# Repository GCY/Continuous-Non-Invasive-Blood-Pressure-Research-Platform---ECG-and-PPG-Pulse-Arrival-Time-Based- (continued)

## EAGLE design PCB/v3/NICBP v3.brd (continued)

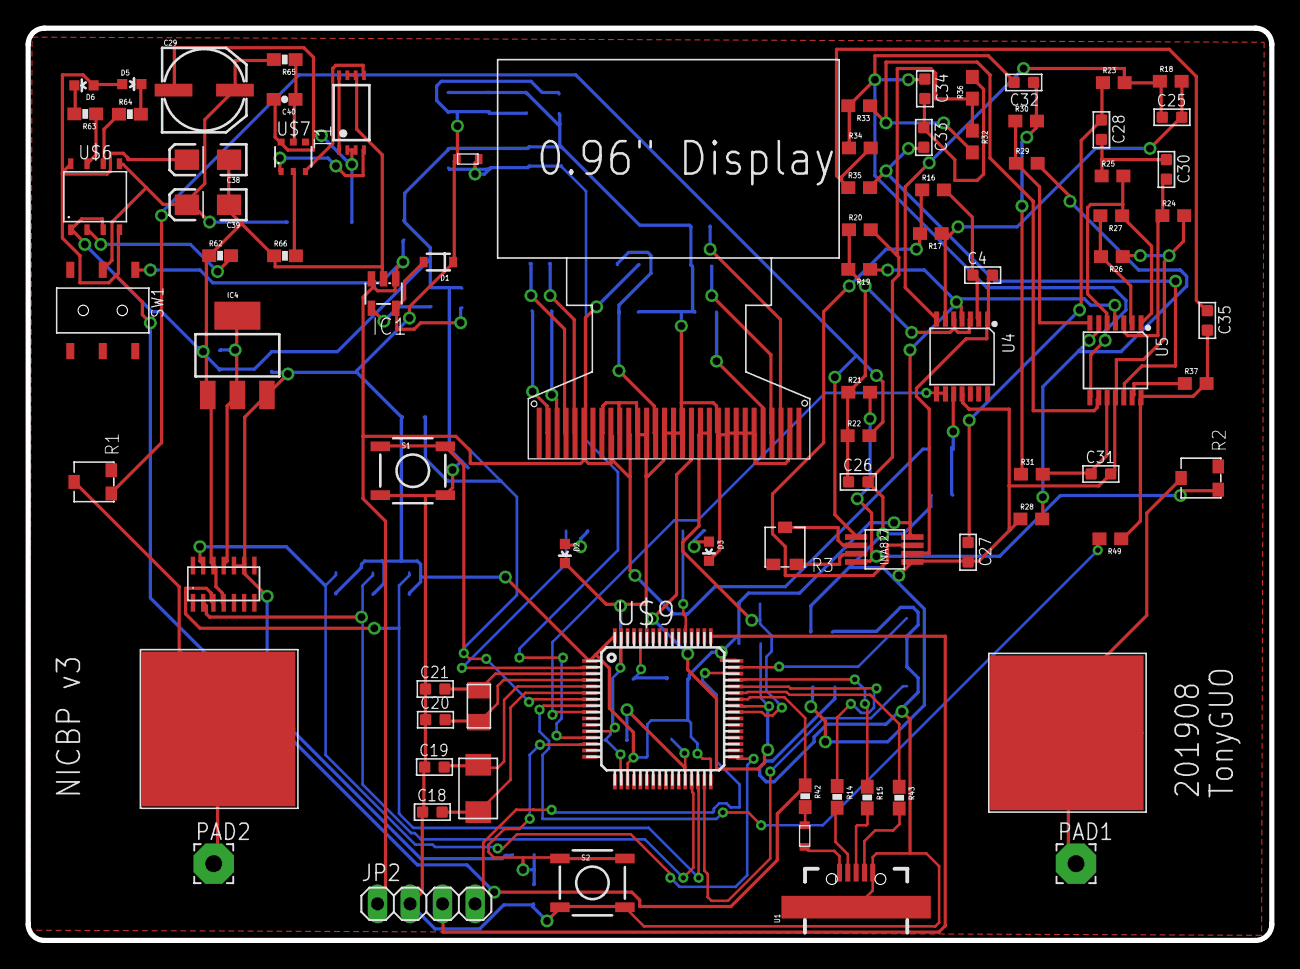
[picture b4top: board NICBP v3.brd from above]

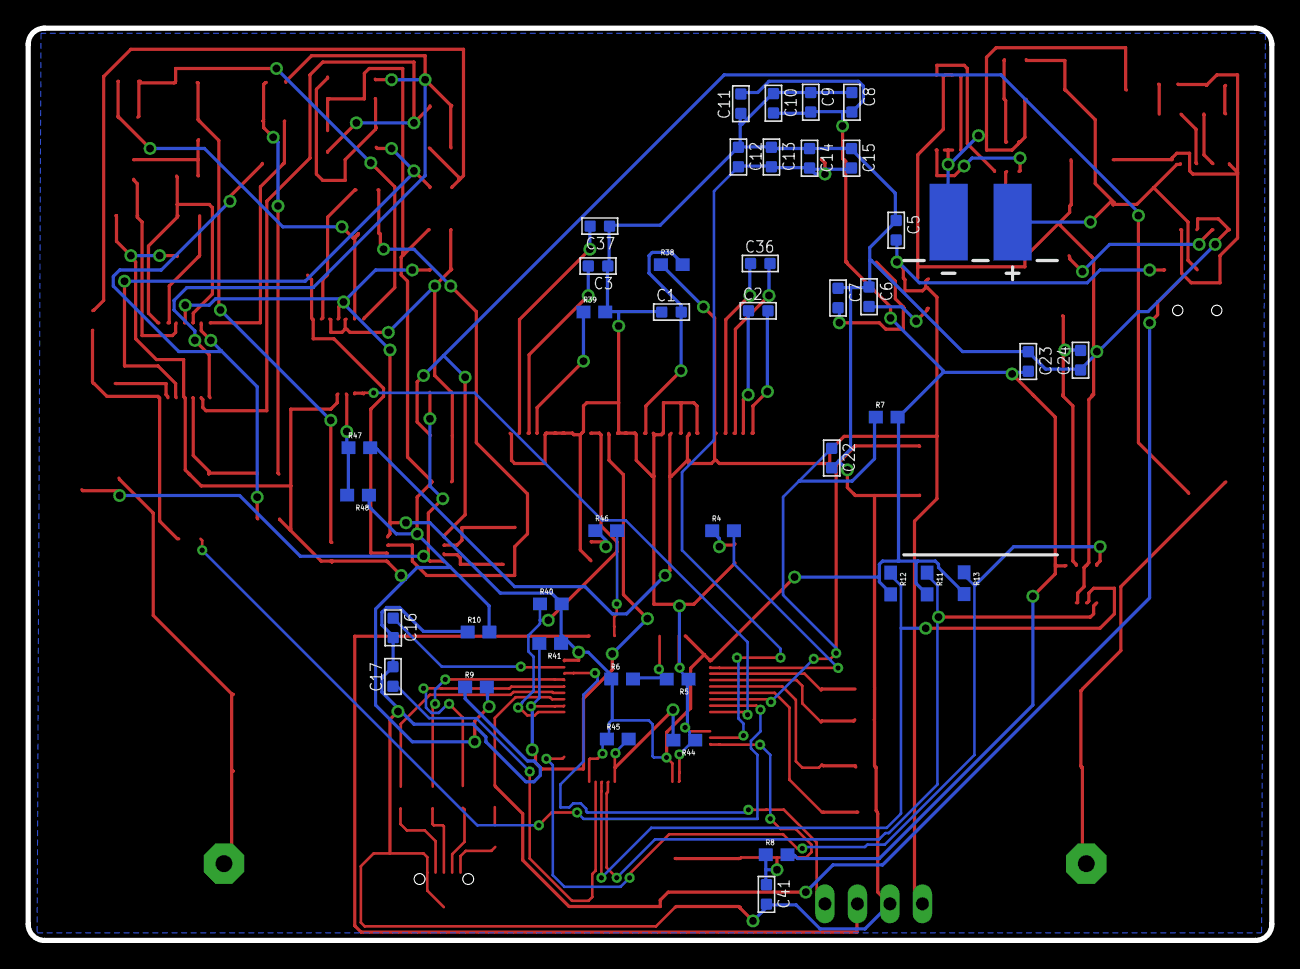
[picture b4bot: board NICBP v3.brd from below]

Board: 2 copper layers, 97.2 x 71.3 mm, 125 parts (42 on the bottom side), 89 nets.

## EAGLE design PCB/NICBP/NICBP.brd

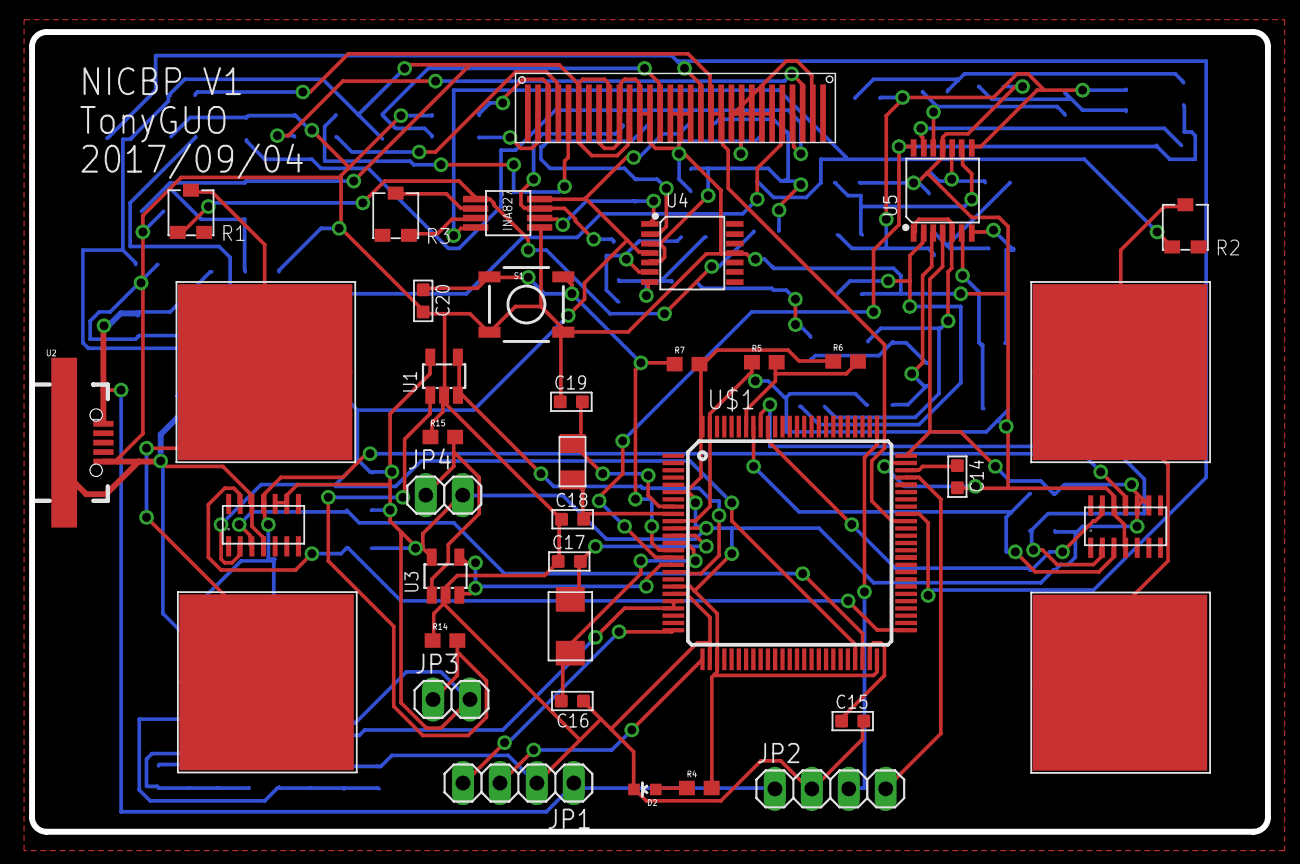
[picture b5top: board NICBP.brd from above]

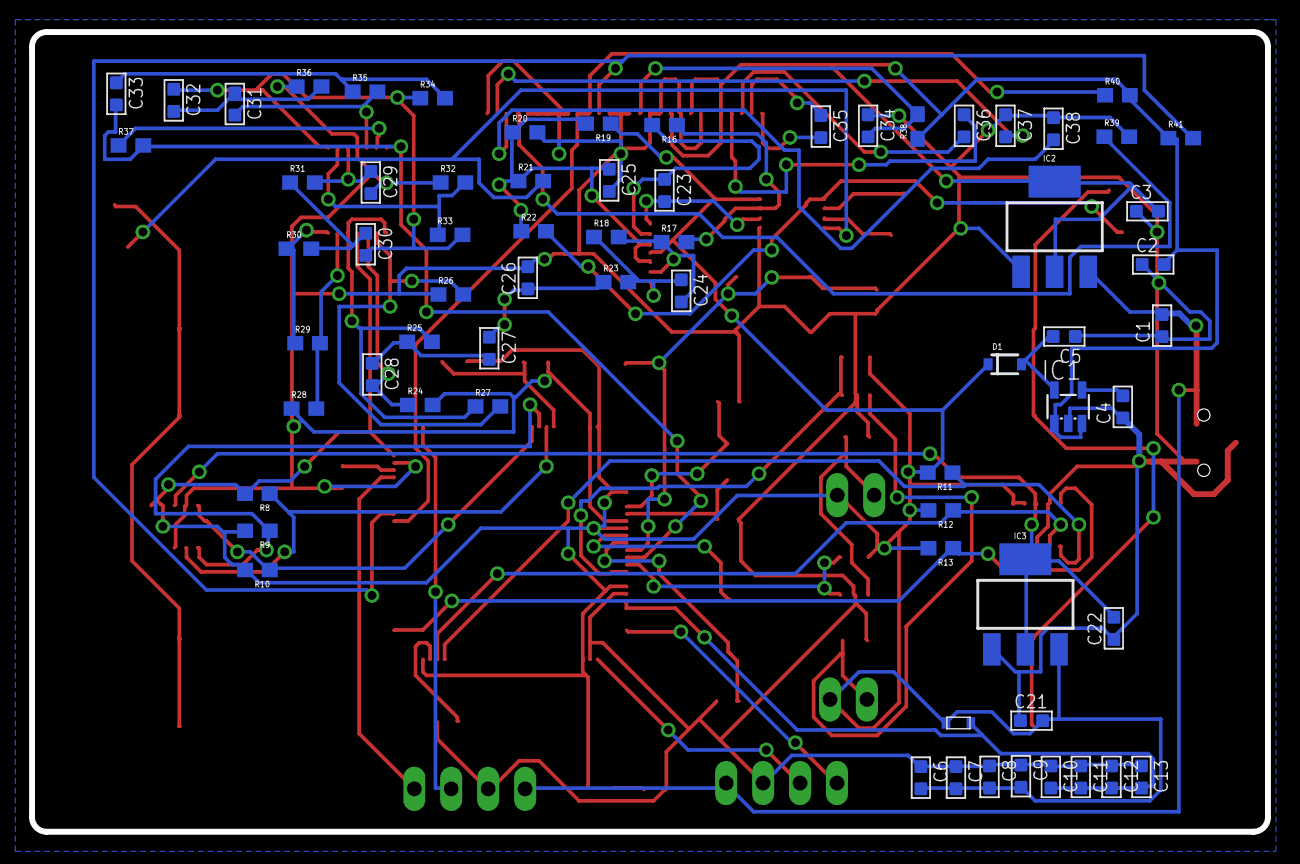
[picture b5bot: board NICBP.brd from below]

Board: 2 copper layers, 85.0 x 55.0 mm, 106 parts (68 on the bottom side), 69 nets.

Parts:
C1, C2, C3, C4, C5, C6, C7, C10, C11, C12, C13, C20, C21, C22, C23, C24, C25, C26, C27, C28, C29, C30, C31, C32, C34: 0.1uf; C0603
C8, C9, C35, C36, C37: 1uf; C0603
C14, C15: 2.2uf; C0603
C16, C17: 22pF; C0603
C18, C19: 12.5pF; C0603
C33: 0.22uf; C0603
C38: 4.7uf; C0603
D1: BAT20JFILM; SOD-323
D2: BLUE; LED-0603
IC1: LD398530RM; SOT23-5L
IC2: LDO_5V; SOT223
IC3: LDO_1V8; SOT223
JP1, JP2: 1X04
JP3, JP4: 1X02
R1, R2: 1M; TRIMPOT_TC33
R3: 100k; TRIMPOT_TC33
R4: 1k; 0603
R5, R6, R7, R19, R20, R38: 10k; 0603
R8, R9, R10, R11, R12, R13, R40, R41: 4.7k; 0603
R14, R15: 3k; 0603
R16: 1M; 0603
R17, R18, R27: 5.1k; 0603
R21, R22: 2M; 0603
R23: 100; 0603
R24, R25: 1.8M; 0603
R26, R28, R32, R37: 12k; 0603
R29: 100k; 0603
R30, R31: 7.5k; 0603
R33: 5.6k; 0603
R34, R35: 27k; 0603
R36: 9.1k; 0603
R39: 390k; 0603
S1: TACTILE_SWITCH_SMD
U1, U3: LM32AMF; SOT-23-5
U2: USB-MICRO-SMD
U4, U5: LM324PW-TSSOP14; TSSOP14-0.65-5X4.4MM
U$1: STM32F407V; TQFP100
U$2: NX5032CA-8MHZ
U$3: FCM1608KF-601T03
U$4: 32.768KHZ-FC-135
U$5: INA827
U$6, U$7, U$8, U$9: CAPSENSE_PAD
U$10, U$11: MAX30100
U$12: ER-OLED0.96

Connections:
1V8: C22.2, IC3.2, IC3.4, U$10.11, U$11.11
ADC1: C33.2, R37.2, U5.14, U$1.15
ADC2: U3.3, U3.4, U$1.16
ADC3: U1.3, U1.4, U$1.17
GND: C1.1, C2.1, C3.1, C4.1, C5.1, C6.1, C7.1, C8.1, C9.1, C10.1, C11.1, C12.1, C13.1, C14.2, C15.2, C16.1, C17.1, C18.1, C19.1, C20.2, C21.1, C22.1, C25.2, C26.2, C29.2, C34.1, C37.1, C38.1, D2.C, IC1.2, IC2.1, IC3.1, JP1.2, JP2.2, R5.1, R14.1, R15.1, R20.2, R24.2, R26.1, R28.1, R32.1, R36.1, R39.2, S1.3, S1.4, U1.2, U2.GND, U2.GND1, U3.2, U4.11, U5.11, U$1.10, U$1.20, U$1.27, U$1.74, U$1.99, U$5.5, U$10.4, U$10.12, U$11.4, U$11.12, U$12.P$8, U$12.P$10, U$12.P$12, U$12.P$13, U$12.P$15, U$12.P$16, U$12.P$17, U$12.P$21, U$12.P$22, U$12.P$23, U$12.P$24, U$12.P$25, U$12.P$29
I2C1_SCL: R9.1, U$1.92, U$10.2
I2C1_SDA: R8.1, U$1.93, U$10.3
I2C2_SCL: R11.1, U$1.47, U$11.2
I2C2_SDA: R12.1, U$1.48, U$11.3
I2C3_SCL: R41.2, U$1.67, U$12.P$18
I2C3_SDA: R40.1, U$1.66, U$12.P$19, U$12.P$20
INT_EXTI5: R10.1, U$1.91, U$10.13
INT_EXTI12: R13.1, U$1.51, U$11.13
L_ARM: R1.2, U$8.P$1, U$8.P$2, U$9.P$1, U$9.P$2
MCU_3V3: C6.2, C7.2, C8.2, C9.2, C21.2, D1.1, IC3.3, JP3.2, JP4.2, R4.2, R6.1, R7.2, R8.2, R9.2, R10.2, R11.2, R12.2, R13.2, R19.1, U1.5, U3.5, U4.4, U5.4, U$1.6, U$1.11, U$1.19, U$1.28, U$1.50, U$1.75, U$1.100, U$3.1, U$5.8, U$10.9, U$10.10, U$11.9, U$11.10
unnamed: D2.A, R4.1
unnamed: C15.1, U$1.49
unnamed: C14.1, U$1.73
unnamed: R5.2, R6.2, U$1.94
unnamed: C20.1, R7.1, S1.1, S1.2, U$1.14
unnamed: C4.2, IC1.4
unnamed: C5.2, D1.2, IC1.5
unnamed: R3.3, U$5.3
unnamed: JP4.1, R15.2, U3.1
unnamed: JP3.1, R14.2, U1.1
unnamed: R3.2, U$5.2
unnamed: C23.2, U4.1, U$5.6
unnamed: R1.1, R22.2, U$5.1
unnamed: R2.1, R21.2, U$5.4
unnamed: C23.1, R16.2, U4.2
unnamed: R16.1, R17.2, U$5.7
unnamed: C24.2, R17.1, R18.2, U4.6
unnamed: C25.1, R19.2, R20.1, R21.1, R22.1, U4.3, U4.5
unnamed: C24.1, R18.1, R23.2, U4.7
unnamed: C26.1, C27.1, R23.1
unnamed: R26.2, R27.2, U5.2
unnamed: R25.2, R27.1, U5.1, U5.5
unnamed: C28.2, R24.1, U5.3
unnamed: C27.2, C28.1, R25.1
unnamed: R28.2, R29.2, U5.6
unnamed: R29.1, R30.1, U5.7
unnamed: C30.1, R30.2, R31.1
unnamed: C29.1, R31.2, U5.10
unnamed: C30.2, C32.1, R33.2, R34.1, U5.8
unnamed: R32.2, R33.1, U5.9
unnamed: C33.1, R34.2, R35.1
unnamed: C31.1, C32.2, R36.2
unnamed: C34.2, R38.2, U$12.P$14
unnamed: C31.2, R35.2, U5.12
unnamed: R37.1, U5.13
unnamed: C35.1, U$12.P$3
unnamed: C36.1, U$12.P$5
unnamed: C35.2, U$12.P$2
unnamed: C36.2, U$12.P$4
unnamed: R39.1, U$12.P$26
unnamed: C38.2, U$12.P$27
unnamed: C37.2, U$12.P$28
OSC32_IN: C19.2, U$1.8, U$4.1
OSC32_OUT: C18.2, U$1.9, U$4.2
OSC_IN: C17.2, U$1.12, U$2.1
OSC_OUT: C16.2, U$1.13, U$2.2
R_ARM: R2.2, U$6.P$1, U$6.P$2, U$7.P$1, U$7.P$2
SWTCK: JP2.3, U$1.76
SWTDIO: JP2.4, U$1.72
UART2_RX: JP1.3, U$1.26
UART2_TX: JP1.4, U$1.25
VCC: C1.2, IC2.3, JP1.1, JP2.1, U2.VBUS1
VDD: C2.2, C3.2, IC1.1, IC1.3, IC2.2, IC2.4, R38.1, R40.2, R41.1, U$12.P$6, U$12.P$9, U$12.P$11
VDDA: C10.2, C11.2, C12.2, C13.2, U$1.21, U$1.22, U$3.2

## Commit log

2018-10-02 Test Firmware
2018-10-02 Circuit and Layout Eagle project
2018-10-02 image
2018-10-03 algorithm
2019-07-22 clip
2019-08-23 NICBP v1
2019-08-23 delete
2019-09-30 version 3 Reduce parts and USB-FS VCP
2019-09-30 firmware for hardware test
2019-09-30 TP4056 just suck
2020-06-08 add res
2020-06-17 add ver 1
2020-06-17 move to PCB
2020-06-18 v3 demo
2020-06-19 Display PPG-Signal, SpO2-Value, ECG-Signal
2020-06-19 PAT Calc
2020-06-21 add ECG Board Reference Design
2020-07-08 Create LICENSE
2020-07-14 add OSHWA logo

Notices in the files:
parts and their libraries:
SparkFun-Electromechanical: Licensing: CC v3.0 Share-Alike You are welcome to use this library for commercial purposes.
